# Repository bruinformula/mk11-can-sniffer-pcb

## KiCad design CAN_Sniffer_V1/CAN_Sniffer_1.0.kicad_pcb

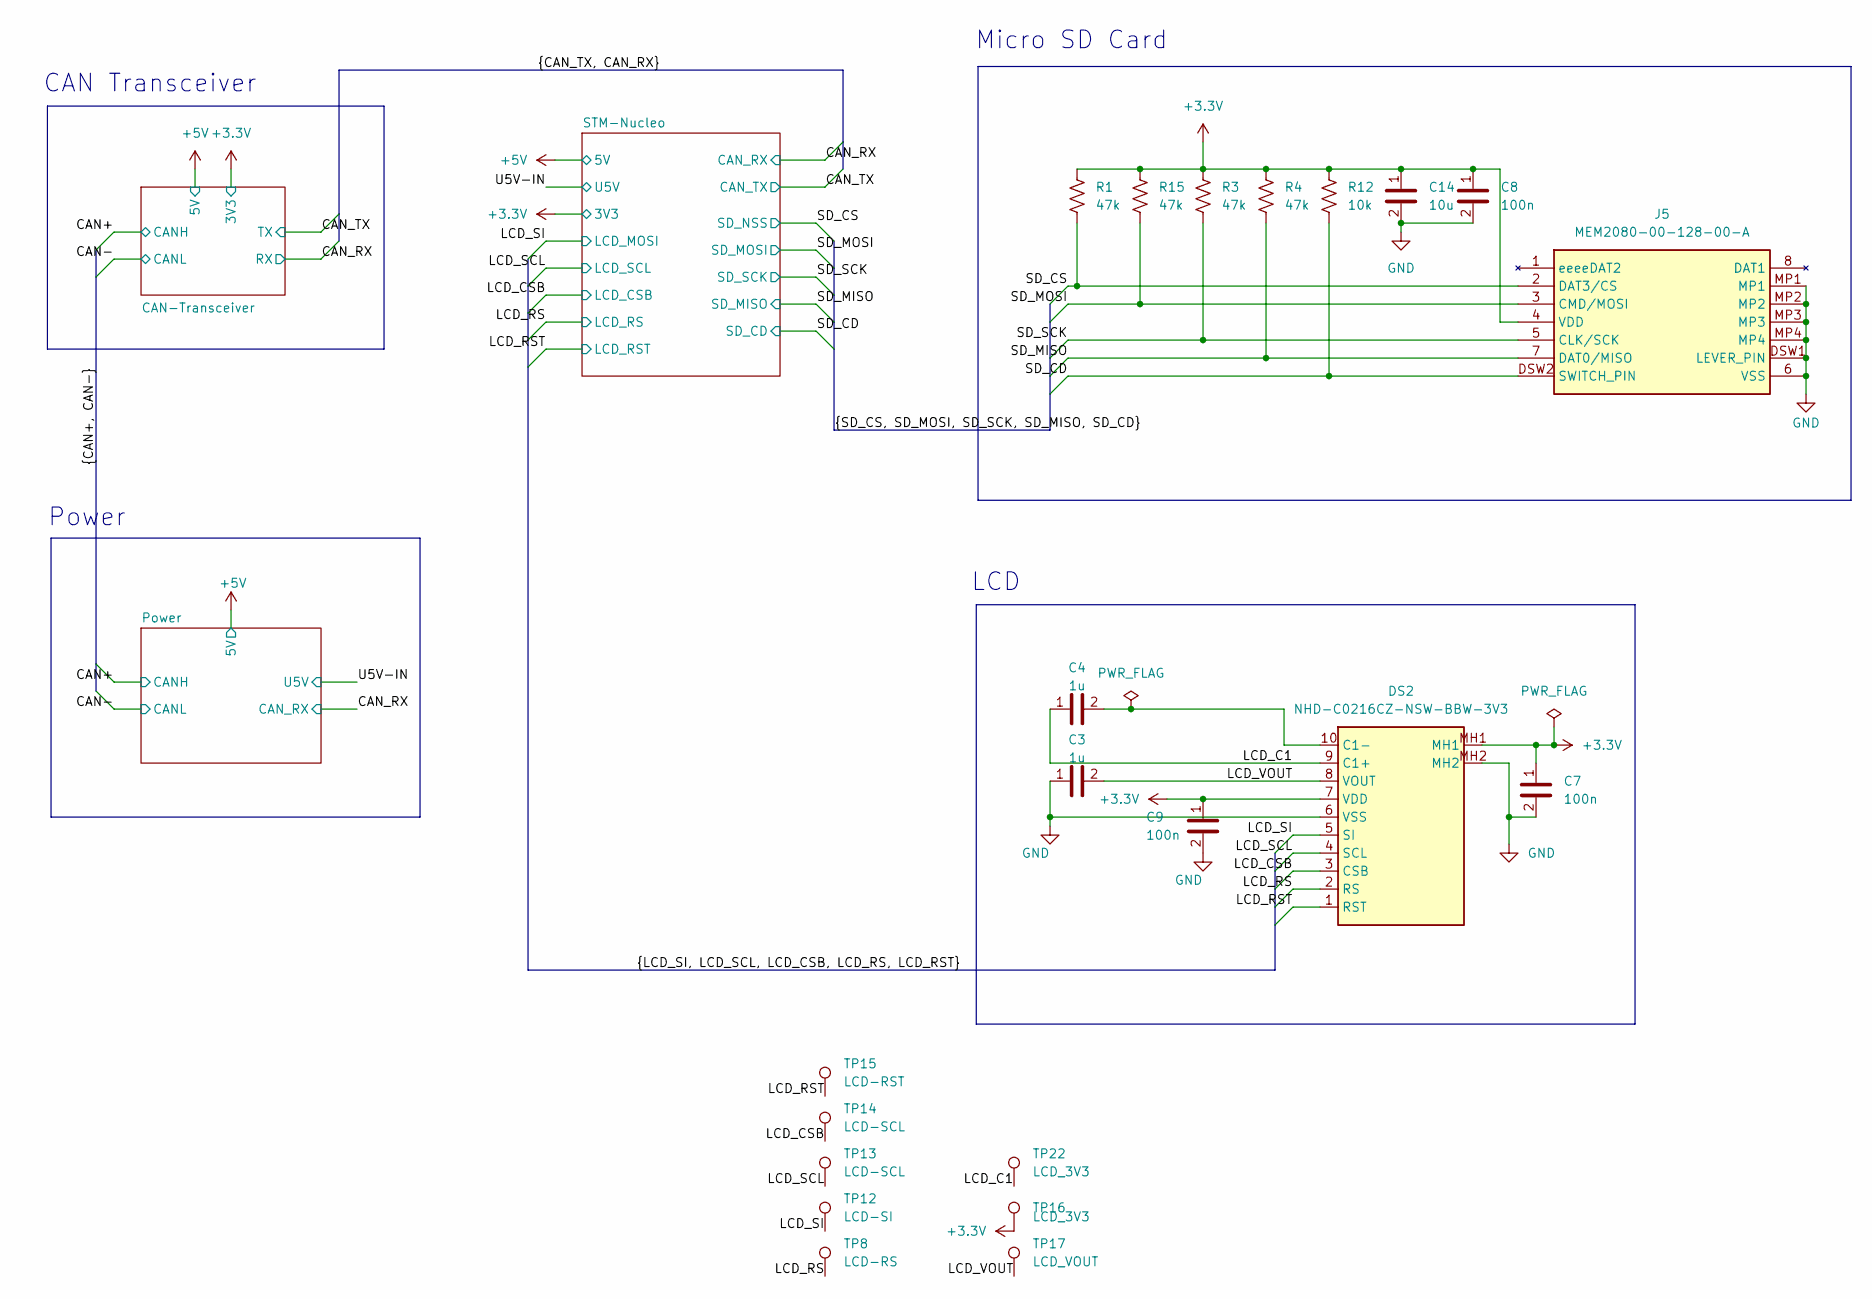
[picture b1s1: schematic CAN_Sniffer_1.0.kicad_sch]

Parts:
C3, C4: 1u; C_0603_1608Metric_Pad1.08x0.95mm_HandSolder; Mouser P/N 963-MAJCT168BB7105KT
C7, C8, C9: 100n; C_0603_1608Metric_Pad1.08x0.95mm_HandSolder; Mouser P/N 581-06035C104KAT2A; Digikey P/N 478-KGM15BR71H104KTCT-ND
C14: 10u; C_0603_1608Metric_Pad1.08x0.95mm_HandSolder; Mouser P/N 81-GRM188R61E106MA3D
DS2: NHD-C0216CZ-NSW-BBW-3V3; NHDC0216CZNSWBBW3V3; Mouser Part Number 763-C0216CZ-NSWBBW3V
J5: MEM2080-00-128-00-A; MEM20800012800A; Mouser Part Number 640-MEM2080-0012800A
R1, R3, R4, R15: 47k; R_0603_1608Metric_Pad0.98x0.95mm_HandSolder; Mouser P/N 708-RMCF0603FT47K0; Digikey P/N RMCF0603FT47K0CT-ND
R12: 10k; R_0603_1608Metric_Pad0.98x0.95mm_HandSolder; Mouser P/N 708-RMCF0603FT10K0; Digikey P/N RMCF0603FT10K0CT-ND
TP8: LCD-RS; TestPoint_Pad_D1.0mm
TP12: LCD-SI; TestPoint_Pad_D1.0mm
TP13, TP14: LCD-SCL; TestPoint_Pad_D1.0mm
TP15: LCD-RST; TestPoint_Pad_D1.0mm
TP16, TP22: LCD_3V3; TestPoint_Pad_D1.0mm
TP17: LCD_VOUT; TestPoint_Pad_D1.0mm

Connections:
+3.3V: C7.1, C8.1, C9.1, C14.1, DS2.7 (VDD), DS2.MH1, J5.4 (VDD), R1.2, R3.2, R4.2, R12.2, R15.2, TP16.1; also elsewhere on the board
/LCD_C1: C4.1, DS2.9 (C1+), TP22.1
/LCD_CSB: DS2.3 (CSB), TP14.1; also elsewhere on the board
/LCD_RS: DS2.2 (RS), TP8.1; also elsewhere on the board
/LCD_RST: DS2.1 (RST), TP15.1; also elsewhere on the board
/LCD_SCL: DS2.4 (SCL), TP13.1; also elsewhere on the board
/LCD_SI: DS2.5 (SI), TP12.1; also elsewhere on the board
/LCD_VOUT: C3.2, DS2.8 (VOUT), TP17.1
/SD_CD: J5.DSW2 (SWITCH_PIN), R12.1; also elsewhere on the board
/SD_CS: J5.2 (DAT3/CS), R1.1; also elsewhere on the board
/SD_MISO: J5.7 (DAT0/MISO), R4.1; also elsewhere on the board
/SD_MOSI: J5.3 (CMD/MOSI), R15.1; also elsewhere on the board
/SD_SCK: J5.5 (CLK/SCK), R3.1; also elsewhere on the board
GND: C3.1, C7.2, C8.2, C9.2, C14.2, DS2.6 (VSS), DS2.MH2, J5.6 (VSS), J5.DSW1 (LEVER_PIN), J5.MP1, J5.MP2, J5.MP3, J5.MP4; also elsewhere on the board
unnamed: C4.2, DS2.10 (C1-)

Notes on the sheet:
LCD
Power
Micro SD Card
CAN Transceiver

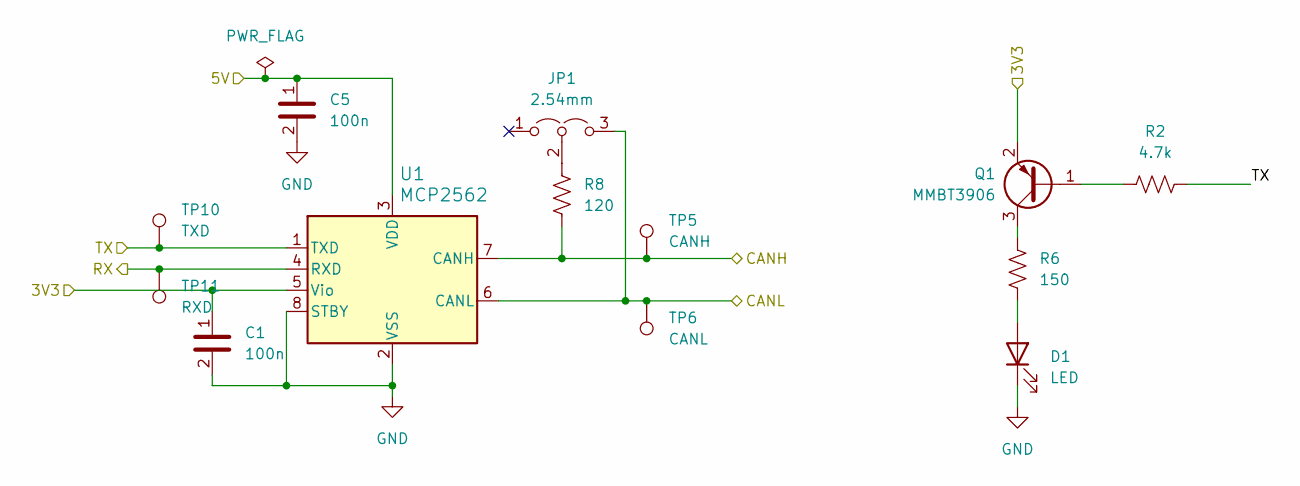
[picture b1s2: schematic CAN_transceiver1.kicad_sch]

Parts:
C1, C5: 100n; C_0805_2012Metric_Pad1.18x1.45mm_HandSolder; Mouser P/N 581-08051C104KAT4A
D1: LED; LED_0805_2012Metric_Pad1.15x1.40mm_HandSolder
JP1: 2.54mm; PinHeader_1x03_P2.54mm_Vertical; Mouser P/N 855-M7581-46; Digikey P/N S9337-ND
Q1: MMBT3906; SOT-23
R2: 4.7k; R_0603_1608Metric_Pad0.98x0.95mm_HandSolder; Mouser P/N 708-RMCF0603FT4K70; Digikey P/N RMCF0603FT4K70CT-ND
R6: 150; R_0603_1608Metric_Pad0.98x0.95mm_HandSolder; Mouser P/N 708-RMCF0603FT150R; Digikey P/N RMCF0603FT150RCT-ND
R8: 120; R_0402_1005Metric_Pad0.72x0.64mm_HandSolder; Mouser P/N 708-RMCF0402FT120R; Digikey P/N RMCF0402FT120RCT-ND
TP5: CANH; TestPoint_Pad_D1.0mm
TP6: CANL; TestPoint_Pad_D1.0mm
TP10: TXD; TestPoint_Pad_D1.0mm
TP11: RXD; TestPoint_Pad_D1.0mm
U1: MCP2562; SOIC-8_3.9x4.9mm_P1.27mm; Digikey PN MCP2562FDT-E/SNCT-ND

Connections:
+3.3V: C1.1, Q1.2 (E), U1.5 (Vio); also elsewhere on the board
+5V: C5.1, U1.3 (VDD); also elsewhere on the board
/CAN+: R8.1, TP5.1, U1.7 (CANH); also elsewhere on the board
/CAN-: JP1.3 (B), TP6.1, U1.6 (CANL); also elsewhere on the board
/CAN_RX: TP11.1, U1.4 (RXD); also elsewhere on the board
/CAN_TX: R2.2, TP10.1, U1.1 (TXD); also elsewhere on the board
GND: C1.2, C5.2, D1.1 (K), U1.2 (VSS), U1.8 (STBY); also elsewhere on the board
unnamed: D1.2 (A), R6.1
unnamed: JP1.2 (C), R8.2
unnamed: Q1.1 (B), R2.1
unnamed: Q1.3 (C), R6.2

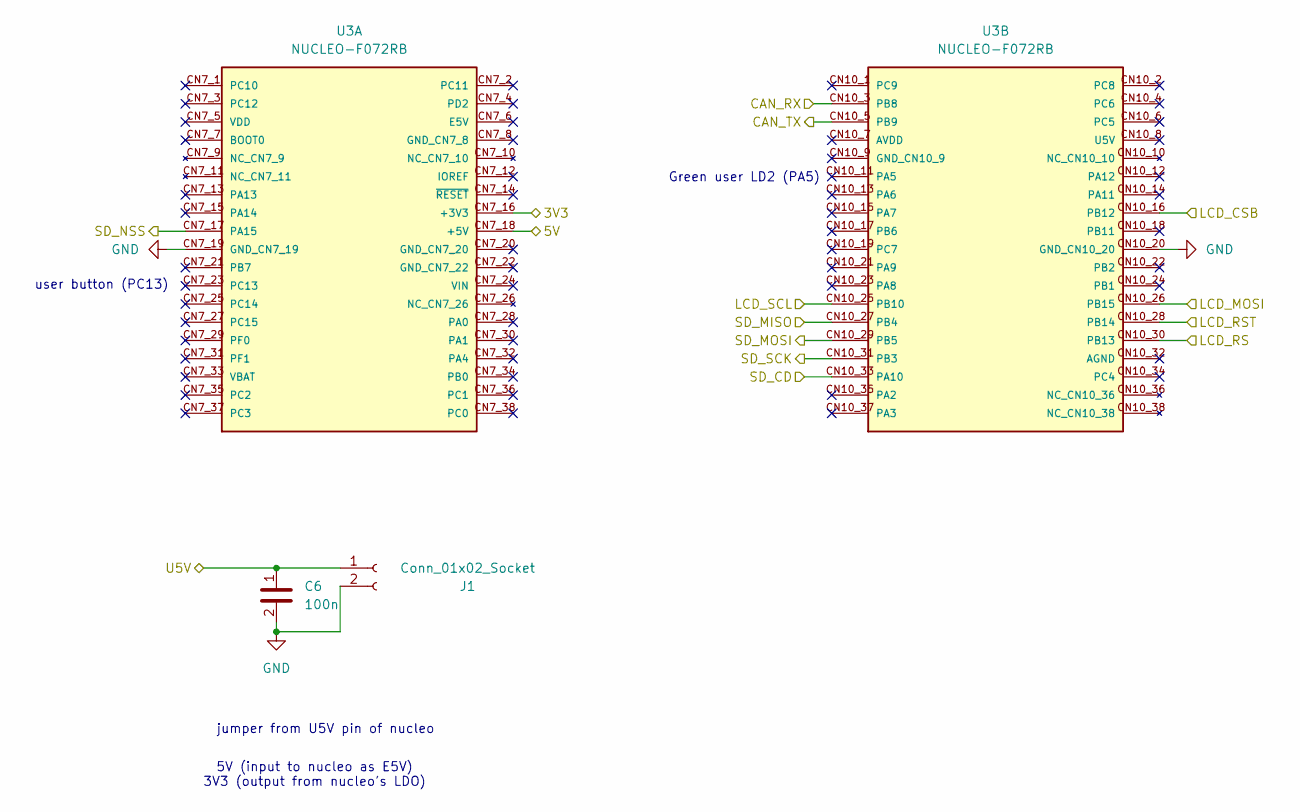
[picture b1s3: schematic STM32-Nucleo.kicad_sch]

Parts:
C6: 100n; C_0805_2012Metric_Pad1.18x1.45mm_HandSolder; Mouser P/N 581-08051C104KAT4A
J1: Conn_01x02_Socket; PinHeader_1x02_P2.54mm_Vertical
U3: NUCLEO-F072RB; MODULE_NUCLEO-F072RB; PARTREV 17

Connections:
+3.3V: U3.CN7_16 (+3V3); also elsewhere on the board
+5V: U3.CN7_18 (+5V); also elsewhere on the board
/CAN_RX: U3.CN10_3 (PB8); also elsewhere on the board
/CAN_TX: U3.CN10_5 (PB9); also elsewhere on the board
/LCD_CSB: U3.CN10_16 (PB12); also elsewhere on the board
/LCD_RS: U3.CN10_30 (PB13); also elsewhere on the board
/LCD_RST: U3.CN10_28 (PB14); also elsewhere on the board
/LCD_SCL: U3.CN10_25 (PB10); also elsewhere on the board
/LCD_SI: U3.CN10_26 (PB15); also elsewhere on the board
/SD_CD: U3.CN10_33 (PA10); also elsewhere on the board
/SD_CS: U3.CN7_17 (PA15); also elsewhere on the board
/SD_MISO: U3.CN10_27 (PB4); also elsewhere on the board
/SD_MOSI: U3.CN10_29 (PB5); also elsewhere on the board
/SD_SCK: U3.CN10_31 (PB3); also elsewhere on the board
/U5V-IN: C6.1, J1.1; also elsewhere on the board
GND: C6.2, J1.2, U3.CN7_19 (GND_CN7_19), U3.CN10_20 (GND_CN10_20); also elsewhere on the board

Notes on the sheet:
user button (PC13)
Green user LD2 (PA5)
jumper from U5V pin of nucleo
5V (input to nucleo as E5V) 3V3 (output from nucleo's LDO)

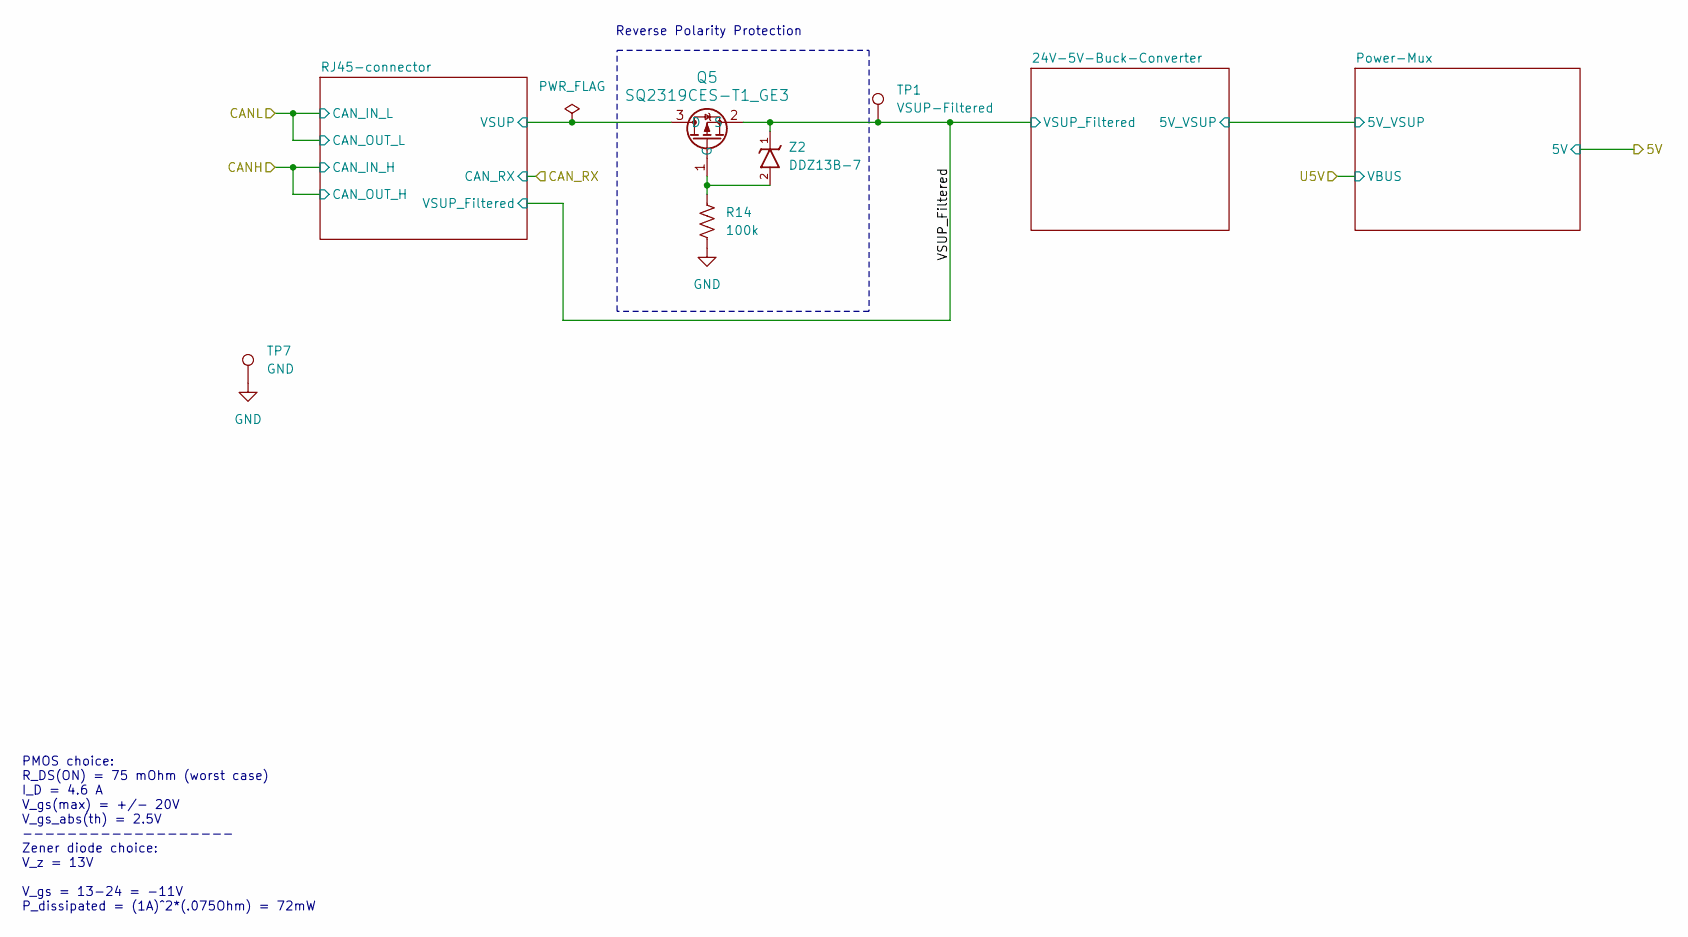
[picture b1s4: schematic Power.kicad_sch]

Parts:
Q5: SQ2319CES-T1_GE3; PMOSGSD_SOT-23_TO-236_VIS
R14: 100k; R_0603_1608Metric_Pad0.98x0.95mm_HandSolder; Mouser P/N 708-RMCF0603FT100K; Digikey P/N RMCF0603FT100KCT-ND
TP1: VSUP-Filtered; TestPoint_Pad_D1.0mm
TP7: GND; TestPoint_Keystone_5015_Micro_Mini
Z2: DDZ13B-7; SOD3716X145N; Mouser Part Number 621-DDZ13B-7

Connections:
/Power/RJ45-connector/VSUP: Q5.3 (D); also elsewhere on the board
/Power/VSUP_Filtered: Q5.2 (S), TP1.1, Z2.1 (K); also elsewhere on the board
GND: R14.1, TP7.1; also elsewhere on the board
unnamed: Q5.1 (G), R14.2, Z2.2 (A)

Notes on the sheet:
PMOS choice: R_DS(ON) = 75 mOhm (worst case) I_D = 4.6 A V_gs(max) = +/- 20V V_gs_abs(th) = 2.5V ------------------- Zener diode choice: V_z = 13V V_gs = 13-24 = -11V P_dissipated = (1A)^2*(.075Ohm) = 72mW
Reverse Polarity Protection

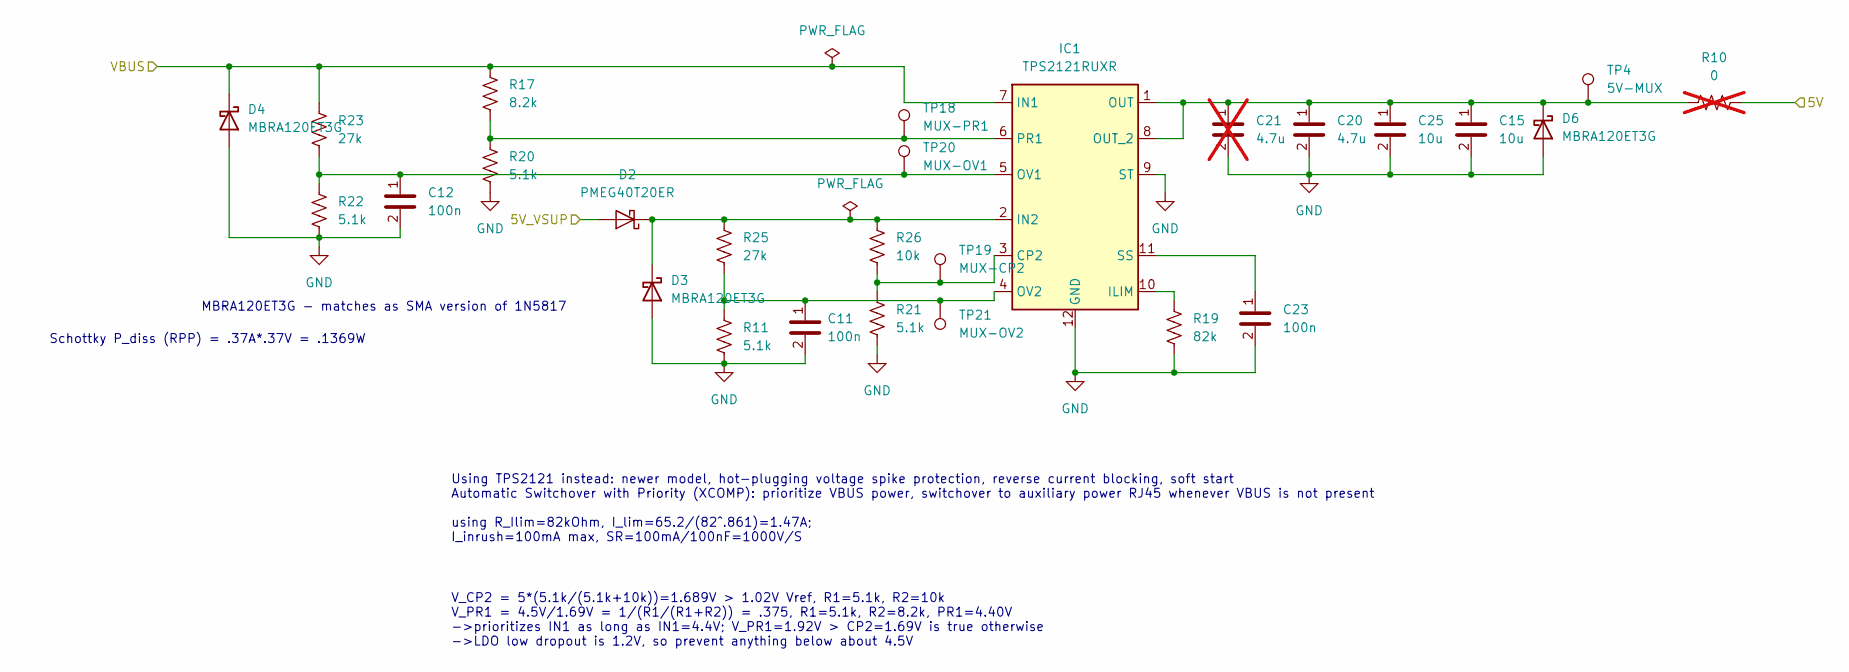
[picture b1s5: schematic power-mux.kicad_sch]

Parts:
C11, C12: 100n; C_0402_1005Metric_Pad0.74x0.62mm_HandSolder; LCSC P/N C307331
C15, C25: 10u; C_0603_1608Metric_Pad1.08x0.95mm_HandSolder; Mouser P/N 81-GRM188R61E106MA3D
C20: 4.7u; C_0603_1608Metric_Pad1.08x0.95mm_HandSolder; LCSC P/N C19666
C21: 4.7u; C_0603_1608Metric_Pad1.08x0.95mm_HandSolder; LCSC P/N C19666; not fitted
C23: 100n; C_0603_1608Metric_Pad1.08x0.95mm_HandSolder; Mouser P/N 581-06035C104KAT2A; Digikey P/N 478-KGM15BR71H104KTCT-ND
D2: PMEG40T20ER; Nexperia_CFP3_SOD-123W
D3, D4, D6: MBRA120ET3G; D_SMA_Handsoldering; Mouser PN MBRA120ET3G
IC1: TPS2121RUXR; Mouser Part Number 595-TPS2121RUXR
R10: 0; R_0805_2012Metric_Pad1.20x1.40mm_HandSolder; Mouser P/N 708-RMCF0805ZT0R00; Digikey P/N RMCF0805ZT0R00CT-ND; not fitted
R11, R20, R21, R22: 5.1k; R_0603_1608Metric_Pad0.98x0.95mm_HandSolder; Mouser P/N 708-RMCF0603FT5K10; Digikey P/N RMCF0603FT5K10CT-ND
R17: 8.2k; R_0603_1608Metric_Pad0.98x0.95mm_HandSolder; Mouser P/N 708-RMCF0603FT8K20; Digikey P/N RMCF0603FT8K20CT-ND
R19: 82k; R_0603_1608Metric_Pad0.98x0.95mm_HandSolder; Mouser P/N 708-RMCF0603FT82K0; Digikey P/N RMCF0603FT82K0CT-ND
R23, R25: 27k; R_0603_1608Metric_Pad0.98x0.95mm_HandSolder; Mouser P/N 708-RMCF0603FT27K0; Digikey P/N RMCF0603FT27K0CT-ND
R26: 10k; R_0603_1608Metric_Pad0.98x0.95mm_HandSolder; Mouser P/N 708-RMCF0603FT10K0; Digikey P/N RMCF0603FT10K0CT-ND
TP4: 5V-MUX; TestPoint_Pad_D1.0mm
TP18: MUX-PR1; TestPoint_Pad_D1.0mm
TP19: MUX-CP2; TestPoint_Pad_D1.0mm
TP20: MUX-OV1; TestPoint_Pad_D1.0mm
TP21: MUX-OV2; TestPoint_Pad_D1.0mm

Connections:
+5V: R10.2; also elsewhere on the board
/U5V-IN: D2.2 (A); also elsewhere on the board
GND: C11.2, C12.2, C15.2, C20.2, C21.2, C23.2, C25.2, D3.2 (A), D4.2 (A), D6.2 (A), IC1.9 (ST), IC1.12 (GND), R11.1, R19.1, R20.1, R21.1, R22.1; also elsewhere on the board
unnamed: C15.1, C20.1, C21.1, C25.1, D6.1 (K), IC1.1 (OUT), IC1.8 (OUT_2), R10.1, TP4.1
unnamed: IC1.3 (CP2), R21.2, R26.1, TP19.1
unnamed: IC1.10 (ILIM), R19.2
unnamed: C12.1, IC1.5 (OV1), R22.2, R23.1, TP20.1
unnamed: C11.1, IC1.4 (OV2), R11.2, R25.1, TP21.1
unnamed: IC1.6 (PR1), R17.1, R20.2, TP18.1
unnamed: C23.1, IC1.11 (SS)

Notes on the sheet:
V_CP2 = 5*(5.1k/(5.1k+10k))=1.689V > 1.02V Vref, R1=5.1k, R2=10k V_PR1 = 4.5V/1.69V = 1/(R1/(R1+R2)) = .375, R1=5.1k, R2=8.2k, PR1=4.40V ->prioritizes IN1 as long as IN1=4.4V; V_PR1=1.92V > CP2=1.69V is true otherwise ->LDO low dropout is 1.2V, so prevent anything below about 4.5V
MBRA120ET3G - matches as SMA version of 1N5817
Using TPS2121 instead: newer model, hot-plugging voltage spike protection, reverse current blocking, soft start Automatic Switchover with Priority (XCOMP): prioritize VBUS power, switchover to auxiliary power RJ45 whenever VBUS is not present using R_Ilim=82kOhm, I_lim=65.2/(82^.861)=1.47A; I_inrus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
Schottky P_diss (RPP) = .37A*.37V = .1369W

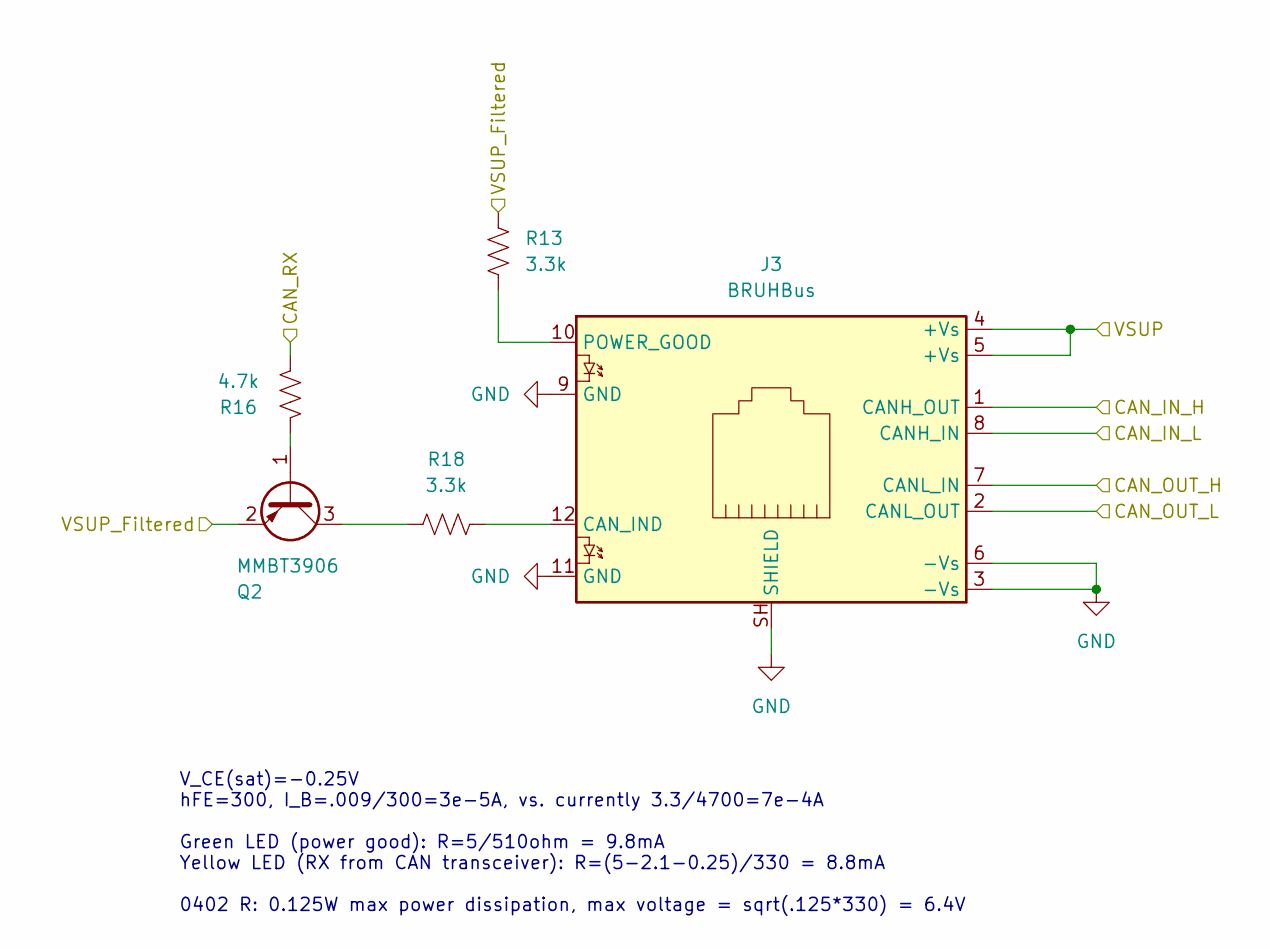
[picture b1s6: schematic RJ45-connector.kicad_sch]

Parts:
J3: BRUHBus; RJ45_Amphenol_RJHSE538X; Manufacturer P/N MTJ-88ARX1-FSM-LG; Digikey P/N 2057-MTJ-88ARX1-FSM-LG-ND
Q2: MMBT3906; SOT-23
R13, R18: 3.3k; R_0603_1608Metric_Pad0.98x0.95mm_HandSolder; Mouser P/N 708-RMCF0603FT3K30; Digikey P/N RMCF0603FT3K30CT-ND
R16: 4.7k; R_0603_1608Metric_Pad0.98x0.95mm_HandSolder; Mouser P/N 708-RMCF0603FT4K70; Digikey P/N RMCF0603FT4K70CT-ND

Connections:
/CAN+: J3.1 (CANH_OUT), J3.8 (CANH_IN); also elsewhere on the board
/CAN-: J3.2 (CANL_OUT), J3.7 (CANL_IN); also elsewhere on the board
/CAN_RX: R16.1; also elsewhere on the board
/Power/RJ45-connector/VSUP: J3.4 (+Vs), J3.5 (+Vs); also elsewhere on the board
/Power/VSUP_Filtered: Q2.2 (E), R13.2; also elsewhere on the board
GND: J3.3 (-Vs), J3.6 (-Vs), J3.9 (GND), J3.11 (GND), J3.SH (SHIELD); also elsewhere on the board
unnamed: J3.12 (CAN_IND), R18.1
unnamed: J3.10 (POWER_GOOD), R13.1
unnamed: Q2.1 (B), R16.2
unnamed: Q2.3 (C), R18.2

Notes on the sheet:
V_CE(sat)=-0.25V hFE=300, I_B=.009/300=3e-5A, vs. currently 3.3/4700=7e-4A Green LED (power good): R=5/510ohm = 9.8mA Yellow LED (RX from CAN transceiver): R=(5-2.1-0.25)/330 = 8.8mA 0402 R: 0.125W max power dissipation, max voltage = sqrt(.125*330) = 6.4V

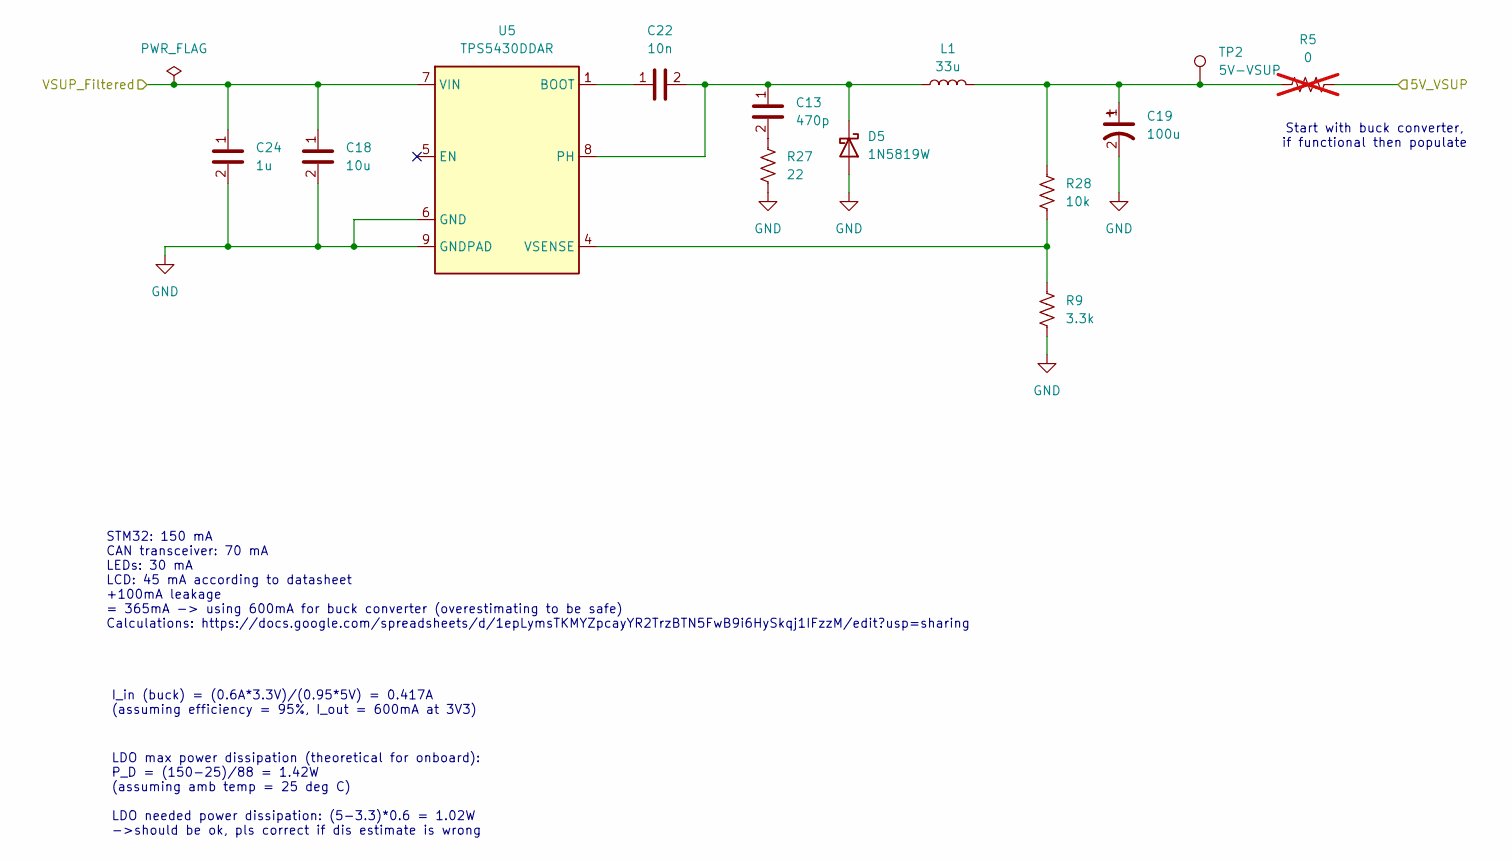
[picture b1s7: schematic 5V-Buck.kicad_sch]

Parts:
C13: 470p; C_0603_1608Metric_Pad1.08x0.95mm_HandSolder; Mouser P/N 581-06035C471J4Z2A
C18: 10u; C_0603_1608Metric_Pad1.08x0.95mm_HandSolder; Mouser P/N 81-GRM188R61E106MA3D
C19: 100u; CP_Radial_D8.0mm_P3.50mm; Mouser P/N 667-EEU-FM1H101; Digikey P/N P12392-ND
C22: 10n; C_0805_2012Metric_Pad1.18x1.45mm_HandSolder; Mouser P/N 581-08055A103JAT2A; Digikey P/N 478-KGM21ACG1H103JUCT-ND
C24: 1u; C_0603_1608Metric_Pad1.08x0.95mm_HandSolder; LCSC P/N C15849
D5: 1N5819W; D_SOD-323_HandSoldering; Mouser P/N 833-B5819WS-TP; LCSC P/N C191023
L1: 33u; IND_CLF7045NIT-330M-D; Digikey P/N 445-174176-6-ND
R5: 0; R_0805_2012Metric_Pad1.20x1.40mm_HandSolder; Mouser P/N 708-RMCF0805ZT0R00; Digikey P/N RMCF0805ZT0R00CT-ND; not fitted
R9: 3.3k; R_0805_2012Metric_Pad1.20x1.40mm_HandSolder; Mouser P/N 708-RMCF0805FT3K30; Digikey P/N RMCF0805FT3K30CT-ND
R27: 22; R_0402_1005Metric_Pad0.72x0.64mm_HandSolder; Mouser P/N 708-RMCF0402FT22R0; Digikey P/N RMCF0402FT22R0CT-ND
R28: 10k; R_0805_2012Metric_Pad1.20x1.40mm_HandSolder; Mouser P/N 708-RMCF0805FT10K0; Digikey P/N RMCF0805FT10K0CT-ND
TP2: 5V-VSUP; TestPoint_Pad_D1.0mm
U5: TPS5430DDAR; TI_SO-PowerPAD-8_ThermalVias; Mouser P/N 595-TPS5430DDAR; Digikey P/N 296-26988-1-ND

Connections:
/Power/VSUP_Filtered: C18.1, C24.1, U5.7 (VIN); also elsewhere on the board
GND: C13.2, C18.2, C19.2, C24.2, D5.2 (A), R9.1, R27.1, R27.2, U5.6 (GND), U5.9 (GNDPAD); also elsewhere on the board
unnamed: C22.1, U5.1 (BOOT)
unnamed: R9.2, R28.1, U5.4 (VSENSE)

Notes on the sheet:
LDO max power dissipation (theoretical for onboard): P_D = (150-25)/88 = 1.42W (assuming amb temp = 25 deg C) LDO needed power dissipation: (5-3.3)*0.6 = 1.02W ->should be ok, pls correct if dis estimate is wrong
STM32: 150 mA CAN transceiver: 70 mA LEDs: 30 mA LCD: 45 mA according to datasheet +100mA leakage = 365mA -> using 600mA for buck converter (overestimating to be safe) Calculations: https://docs.google.com/spreadsheets/d/1epLymsTKMYZpcayYR2TrzBTN5FwB9i6HySkqj1IFzzM/edit?usp=sharing
I_in (buck) = (0.6A*3.3V)/(0.95*5V) = 0.417A (assuming efficiency = 95%, I_out = 600mA at 3V3)
Start with buck converter, if functional then populate

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
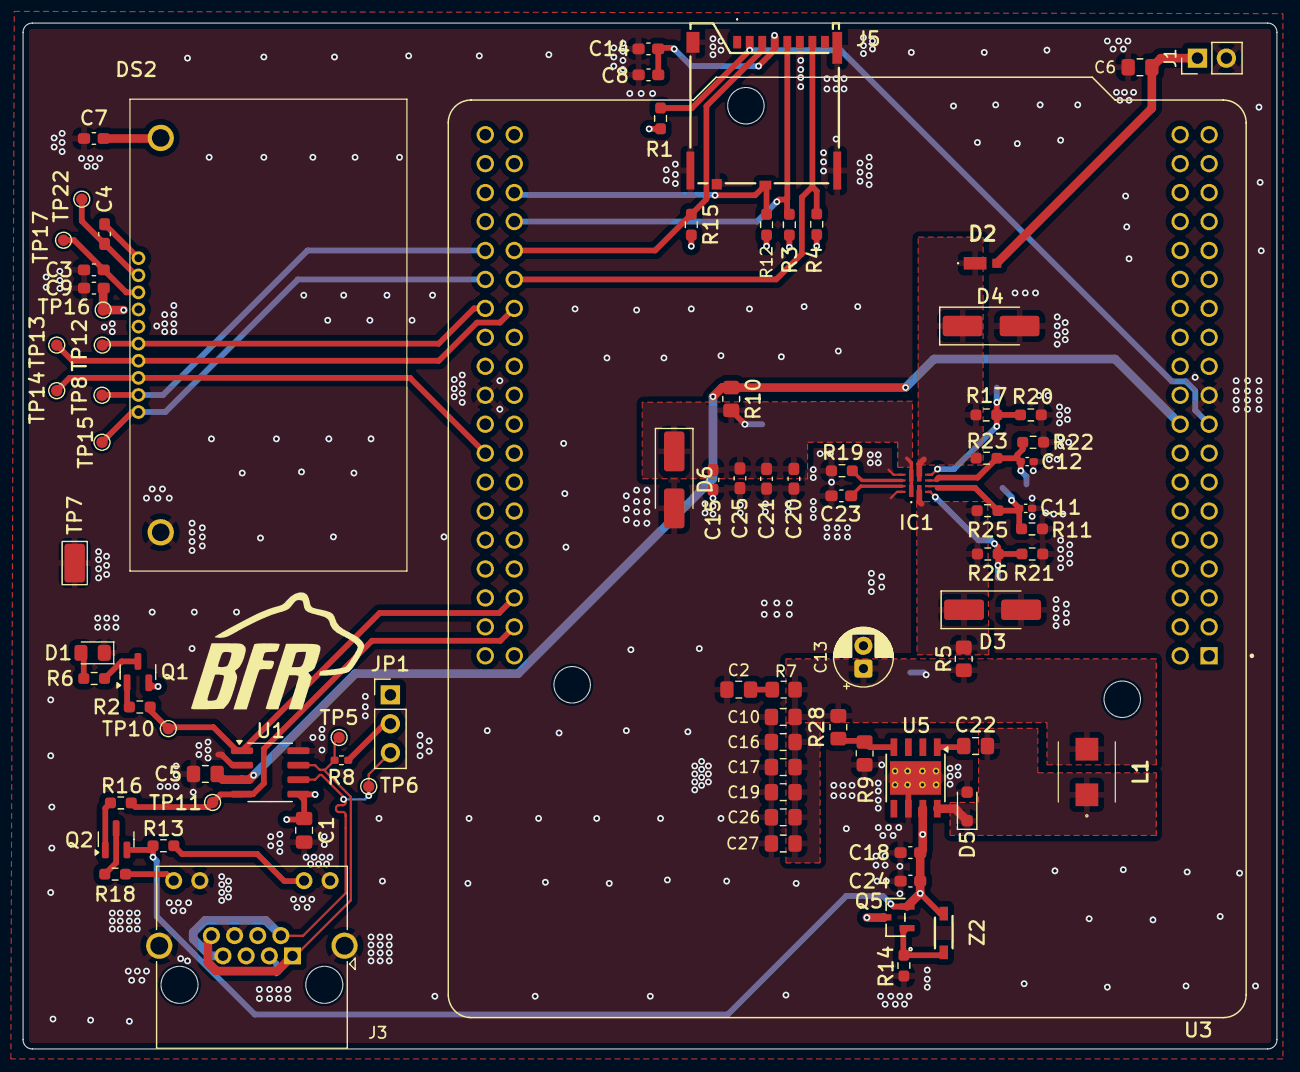
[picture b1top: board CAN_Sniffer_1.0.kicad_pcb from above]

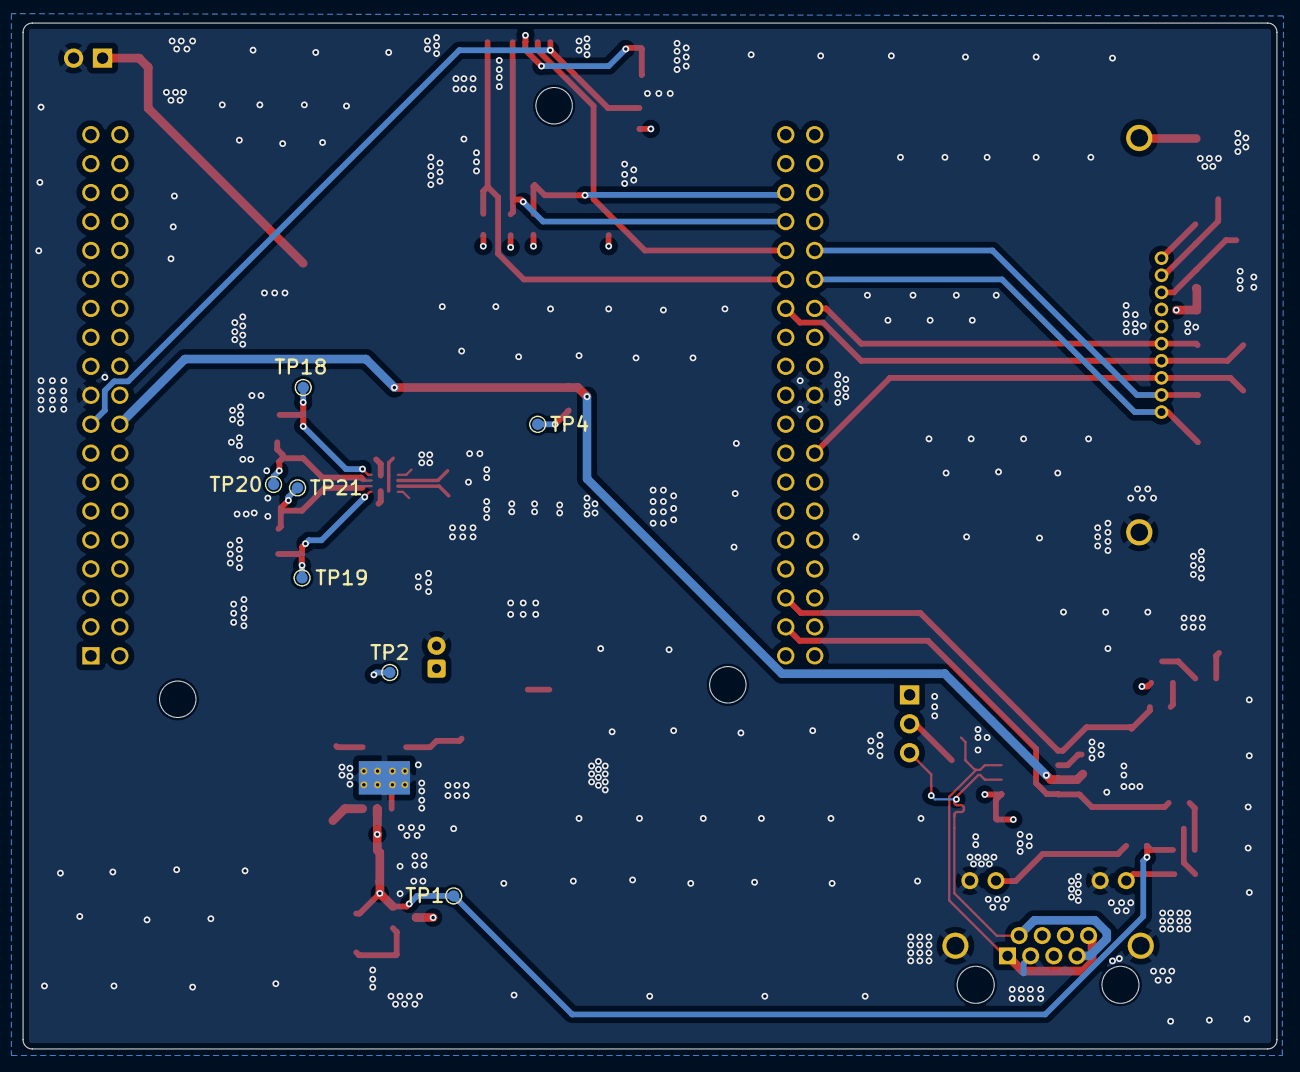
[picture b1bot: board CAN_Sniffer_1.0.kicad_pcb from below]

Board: 4 copper layers, 110.0 x 90.0 mm, 93 parts (7 on the bottom side), 46 nets.

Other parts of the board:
C2: 47u; C_0805_2012Metric_Pad1.18x1.45mm_HandSolder
C10, C16, C17, C26, C27: 4.7u; C_0805_2012Metric_Pad1.18x1.45mm_HandSolder
R7: 1.0; R_0805_2012Metric_Pad1.20x1.40mm_HandSolder

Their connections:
GND: C2.2, C10.2, C16.2, C17.2, C26.2, C27.2; also elsewhere on the board
unnamed: C2.1, R7.1

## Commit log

2025-07-21 Initial commit: CAN transceivers and LDO
2025-08-03 changed power schematics and STM32, added MicroSD card connector and LCD display
2025-08-20 changed power schem, pinouts, first iteration layout
2025-09-27 iteration 2 routing
2026-01-09 sync changes
